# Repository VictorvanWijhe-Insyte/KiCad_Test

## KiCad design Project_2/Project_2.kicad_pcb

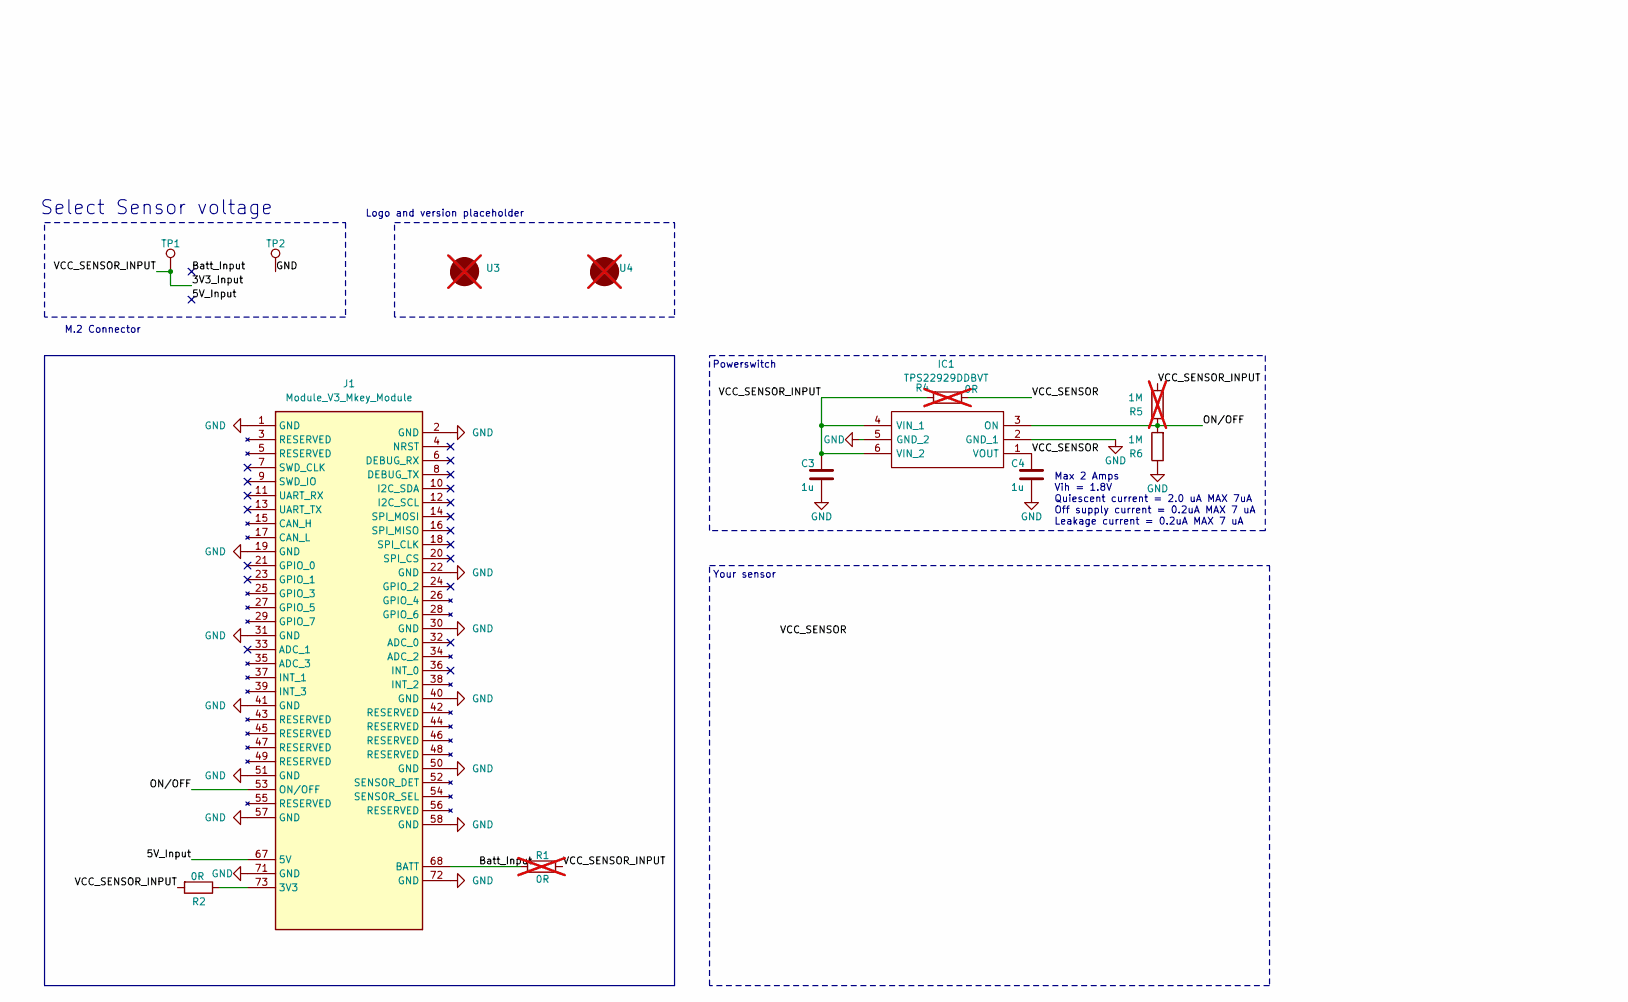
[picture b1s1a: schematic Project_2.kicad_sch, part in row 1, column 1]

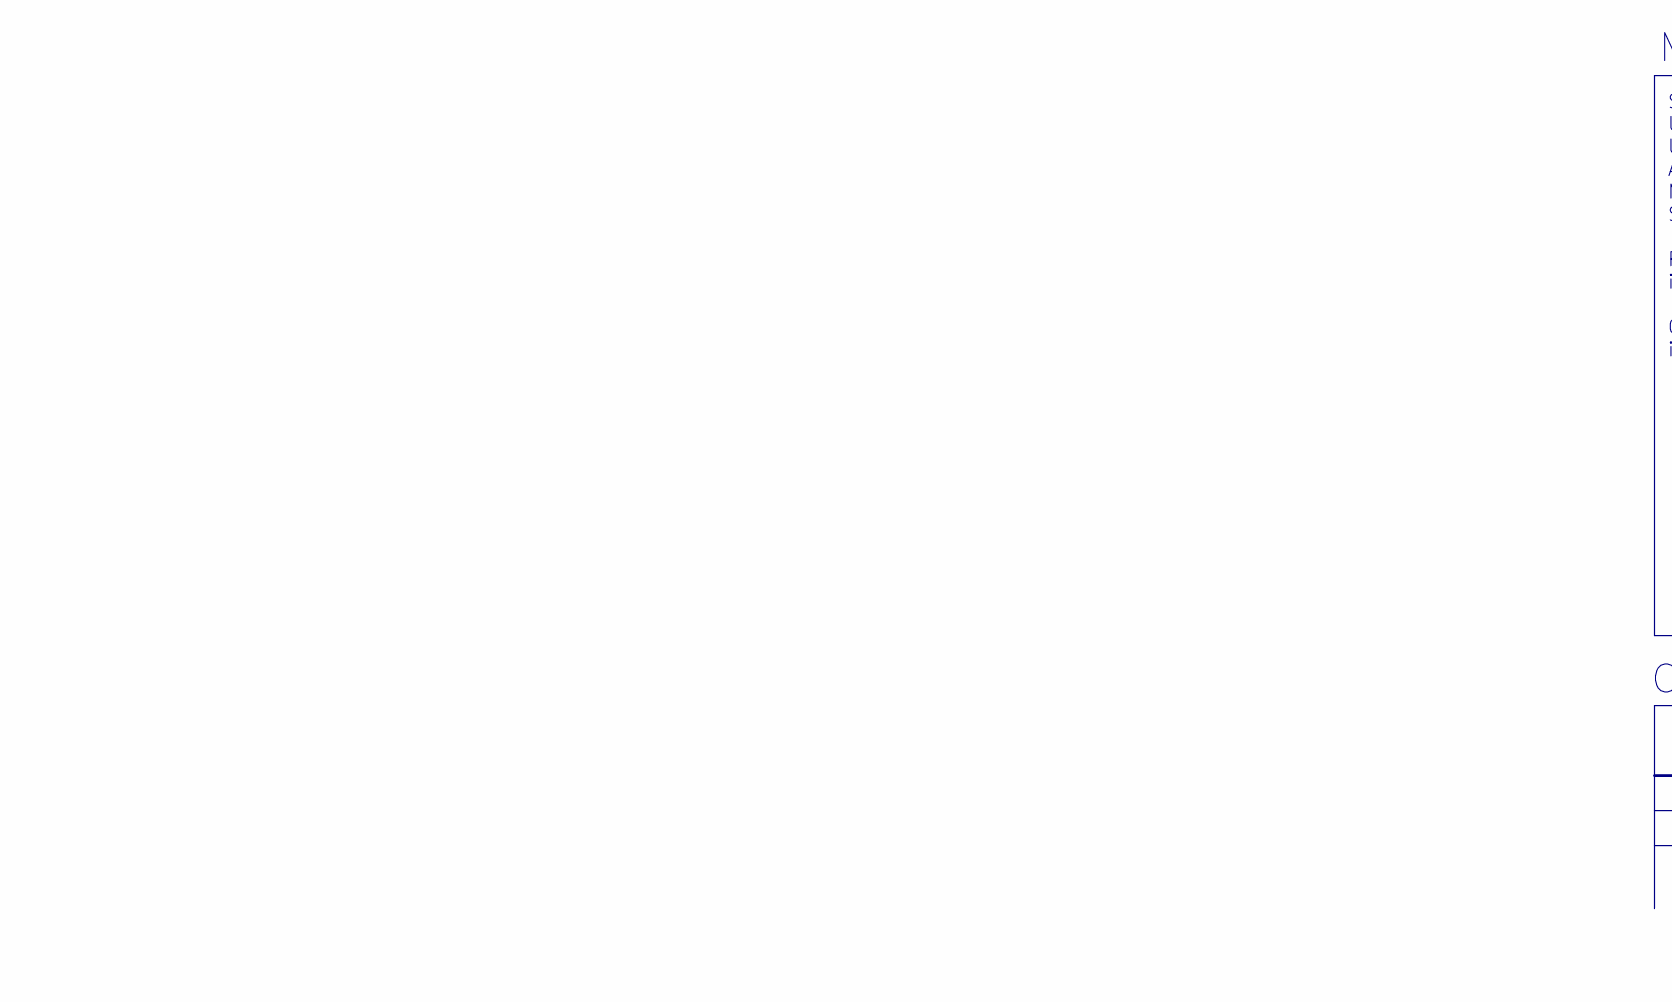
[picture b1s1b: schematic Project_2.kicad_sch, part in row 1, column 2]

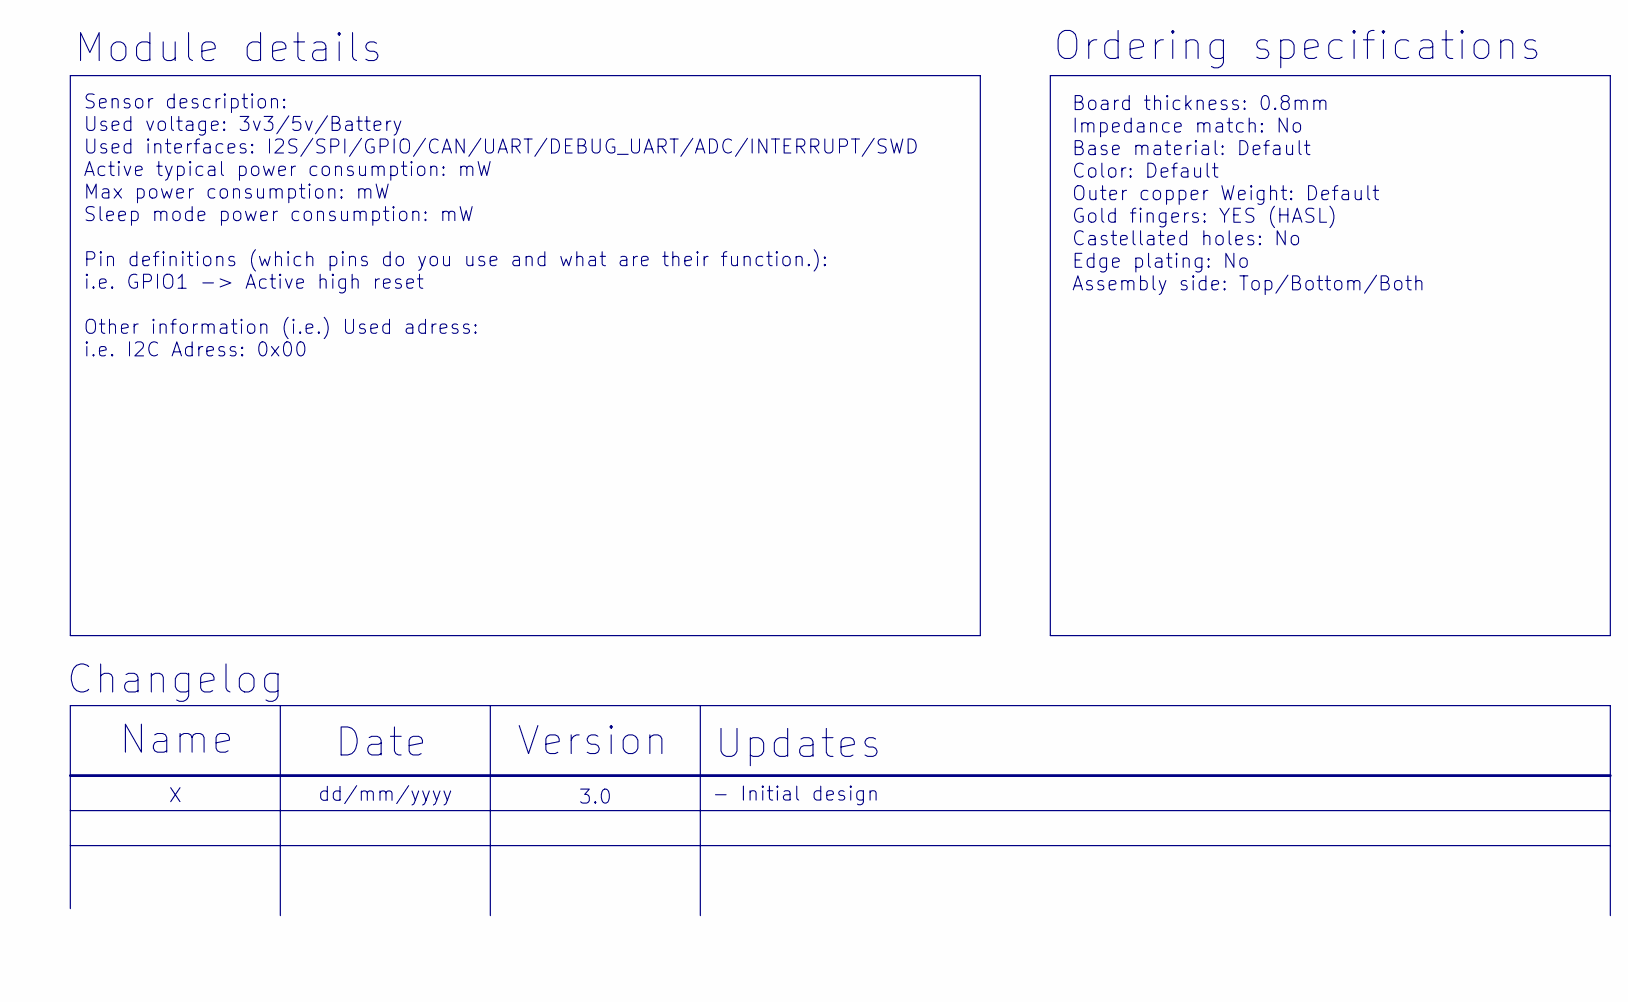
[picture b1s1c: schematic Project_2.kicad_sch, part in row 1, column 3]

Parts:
C3, C4: 1u; C_0603_1608Metric; voltage rating 16V
IC1: TPS22929DDBVT; SOT95P280X145-6N; Mouser Part Number 595-TPS22929DDBVT
J1: Module_V3_Mkey_Module; Module_V3_09x30_Mkey; Mouser Part Number 571-1-2199230-6
R1, R4: 0R; R_0603_1608Metric; not fitted
R2: 0R; R_0603_1608Metric
R5: 1M; R_0603_1608Metric; not fitted
R6: 1M; R_0603_1608Metric
TP1, TP2: TestPoint; TestPoint_Pad_D1.5mm
U3: 3x3_Insyte_Loader; not fitted
U4: Version_Placeholder; not fitted

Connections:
/3V3_Input: C3.1, IC1.4 (VIN_1), IC1.6 (VIN_2), R1.2, R2.2, R4.1, R5.2, TP1.1
/5V_Input: J1.67 (5V)
/Batt_Input: J1.68 (BATT), R1.1
/ON/OFF: IC1.3 (ON), J1.53 (ON/OFF), R5.1, R6.2
/VCC_SENSOR: C4.1, IC1.1 (VOUT), R4.2
GND: C3.2, C4.2, IC1.2 (GND_1), IC1.5 (GND_2), J1.1 (GND), J1.2 (GND), J1.19 (GND), J1.22 (GND), J1.30 (GND), J1.31 (GND), J1.40 (GND), J1.41 (GND), J1.50 (GND), J1.51 (GND), J1.57 (GND), J1.58 (GND), J1.71 (GND), J1.72 (GND), R6.1, TP2.1
unnamed: J1.73 (3V3), R2.1

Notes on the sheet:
3.0
Date
Updates
Version
Module details
Sensor description: Used voltage: 3v3/5v/Battery Used interfaces: I2S/SPI/GPIO/CAN/UART/DEBUG_UART/ADC/INTERRUPT/SWD Active typical power consumption: mW Max power consumption: mW Sleep mode power consumption: mW Pin definitions (which pins do you use and what are their function.): i.e. GPIO1 -> Ac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
Max 2 Amps Vih = 1.8V Quiescent current = 2.0 uA MAX 7uA Off supply current = 0.2uA MAX 7 uA Leakage current = 0.2uA MAX 7 uA
M.2 Connector
Powerswitch
Name
Board thickness: 0.8mm Impedance match: No Base material: Default Color: Default Outer copper Weight: Default Gold fingers: YES (HASL) Castellated holes: No Edge plating: No Assembly side: Top/Bottom/Both
Ordering specifications
- Initial design
Select Sensor voltage
dd/mm/yyyy
Changelog
Your sensor
Logo and version placeholder

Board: 4 copper layers, 14 parts (0 on the bottom side), 6 nets, no tracks yet.

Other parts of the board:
U1: 10x4.1_Insyte_Logo

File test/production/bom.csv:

Designator,Footprint,Quantity,Value,LCSC Part #
"C3, C4",0603,2,1u,
IC1,SOT95P280X145-6N,1,TPS22929DDBVT,C2653763
J1,Module_V3_09x30_Mkey,1,Module_V3_Mkey_Module,
R2,0603,1,0R,
R6,0603,1,1M,
U1,10x4.1_Insyte_Logo,1,~,

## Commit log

2025-08-26 added project
2025-08-26 added project 2
2025-08-26 changed gitigore
